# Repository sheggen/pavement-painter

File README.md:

# Raspberry Pi-controlled pavement painter

Pavement Painter is a Raspberry Pi controlled set of solenoids designed to print images to pavement using rain water. To use the Pavement Painter, you'll need to create the boards included in the Eagle files, as well as a few other controls. 

### WARNING:

Taking on this project is not for the faint at heart; there'll be lots of technical hiccups that you'll run into, and will have to solve on your own. There's hardware in addition to the software that you'll need to create, so get your soldering iron hot.  

## Requirements

- Raspberry Pi
- Python 3
- Everything included in requirements.txt and setup.sh (installable by running ```source setup.sh```)
- Physical boards (layouts included in the Pavement-painter directory)

## Installation

The code comes with a setup script. First do the apt-get installs listed at the beginning of the script. Then, running it should set up a Python Virtual Environment and pip install all the necessary components. Make sure the venv is activated before running the code, to ensure dependencies exist. To run the setup script, at the terminal enter ```source setup.sh```

## Usage

The code can most easily be ran at the terminal by running ```source run_at_boot.sh```. On the Pi, it is recommended that you do NOT run it using Thonny, as it causes a delay that will distort the print. At the terminal, we have yet to experience a delay in the printing outside of the physical limitations of the solenoids. 

## Modifying print parameters

Eventually parameters will be passed in through the above command. For now, though, I've placed all parameters at the ```__init__()``` method of the PavementPainter() class. Modify them and see what happens to your prints!

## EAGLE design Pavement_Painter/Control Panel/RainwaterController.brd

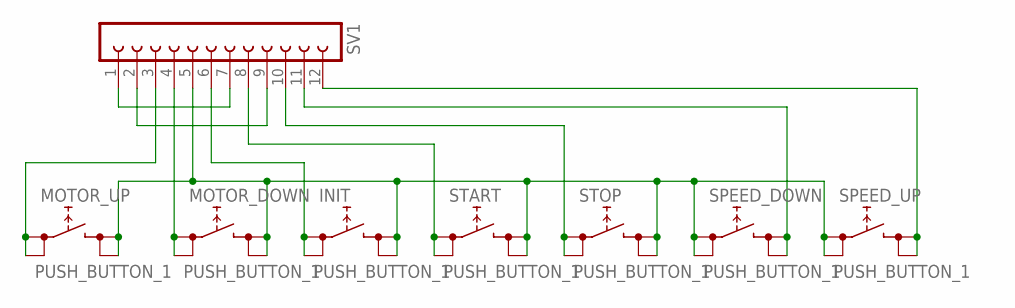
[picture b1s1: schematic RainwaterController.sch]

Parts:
INIT: PUSH_BUTTON_1; PUSHBUTTON
MOTOR_DOWN: PUSH_BUTTON_1; PUSHBUTTON
MOTOR_UP: PUSH_BUTTON_1; PUSHBUTTON
SPEED_DOWN: PUSH_BUTTON_1; PUSHBUTTON
SPEED_UP: PUSH_BUTTON_1; PUSHBUTTON
START: PUSH_BUTTON_1; PUSHBUTTON
STOP: PUSH_BUTTON_1; PUSHBUTTON
SV1: FE12-1; FE12

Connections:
unnamed: MOTOR_UP.P$1 (P1), MOTOR_UP.P$2 (P2), SV1.3
unnamed: SV1.1, SV1.7
unnamed: INIT.P$3 (P3), INIT.P$4 (P4), MOTOR_DOWN.P$3 (P3), MOTOR_DOWN.P$4 (P4), MOTOR_UP.P$3 (P3), MOTOR_UP.P$4 (P4), SPEED_DOWN.P$1 (P1), SPEED_DOWN.P$2 (P2), SPEED_UP.P$1 (P1), SPEED_UP.P$2 (P2), START.P$3 (P3), START.P$4 (P4), STOP.P$3 (P3), STOP.P$4 (P4), SV1.5
unnamed: SV1.2, SV1.9
unnamed: INIT.P$1 (P1), INIT.P$2 (P2), SV1.6
unnamed: START.P$1 (P1), START.P$2 (P2), SV1.8
unnamed: STOP.P$1 (P1), STOP.P$2 (P2), SV1.10
unnamed: MOTOR_DOWN.P$1 (P1), MOTOR_DOWN.P$2 (P2), SV1.4
unnamed: SPEED_DOWN.P$3 (P3), SPEED_DOWN.P$4 (P4), SV1.11
unnamed: SPEED_UP.P$3 (P3), SPEED_UP.P$4 (P4), SV1.12

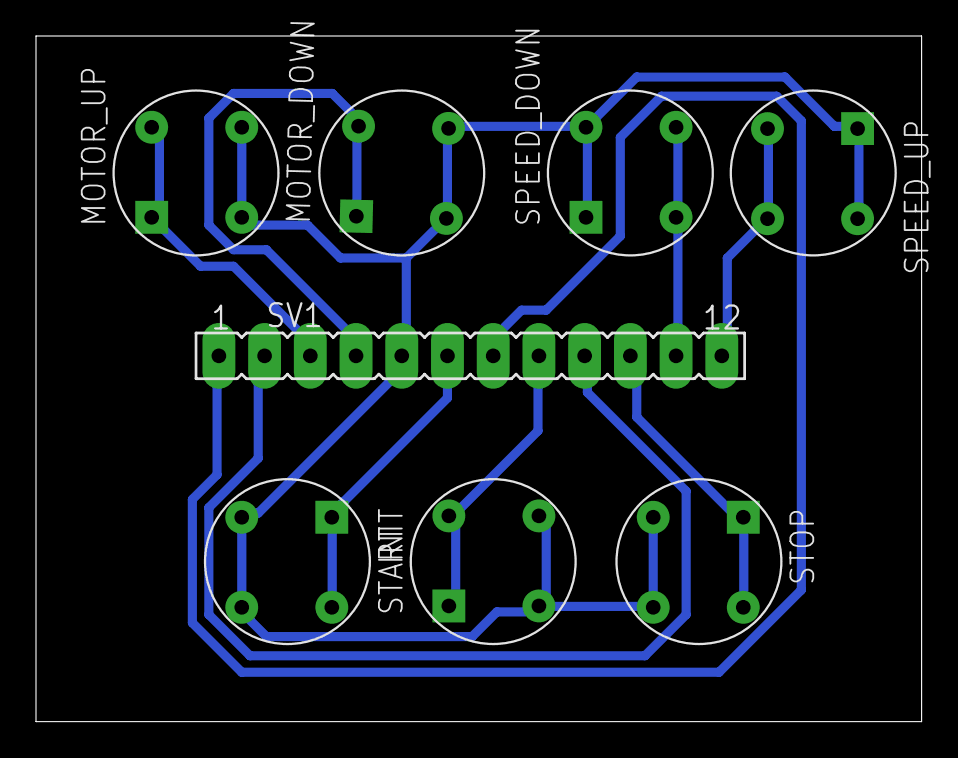
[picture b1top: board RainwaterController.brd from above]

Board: 2 copper layers, 49.2 x 38.1 mm, 8 parts (0 on the bottom side), 10 nets.

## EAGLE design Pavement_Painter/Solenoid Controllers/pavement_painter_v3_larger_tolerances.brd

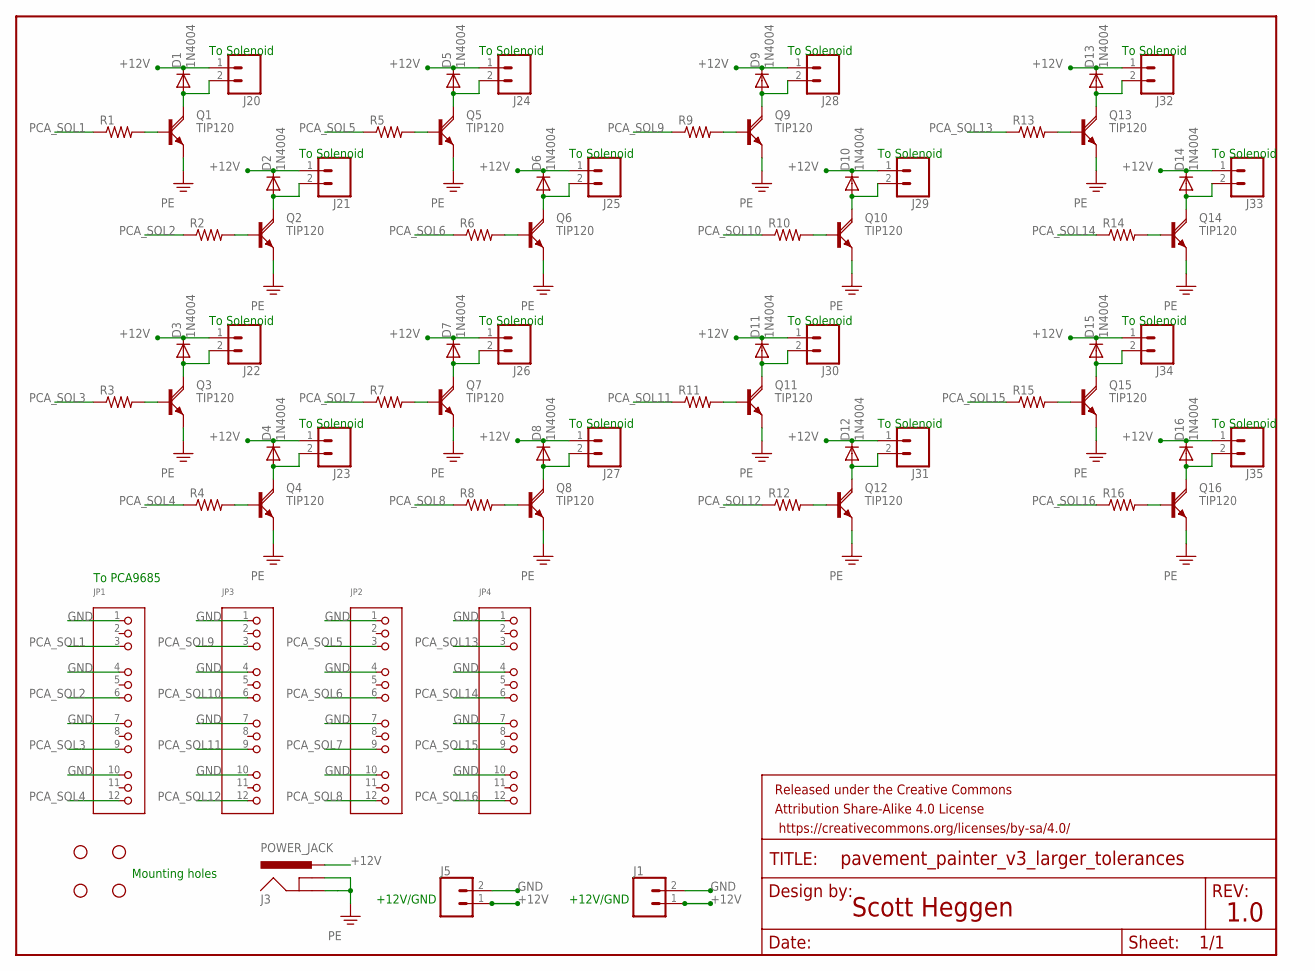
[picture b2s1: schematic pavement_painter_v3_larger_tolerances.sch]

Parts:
D1, D2, D3, D4, D5, D6, D7, D8, D9, D10, D11, D12, D13, D14, D15, D16: 1N4004; DO41-10
FRAME1: FRAME-LETTER; CREATIVE_COMMONS
H1, H2, H3, H4: STAND-OFF
J1, J5, J20, J21, J22, J23, J24, J25, J26, J27, J28, J29, J30, J31, J32, J33, J34, J35: CONN_02SCREWTERMINAL-200MIL-400MIL; SCREWTERMINAL-5MM-2-400MIL
J3: POWER_JACK; POWER_JACK_PTH
JP1, JP2, JP3, JP4: HEADER-3X04; 3X04
Q1, Q2, Q3, Q4, Q5, Q6, Q7, Q8, Q9, Q10, Q11, Q12, Q13, Q14, Q15, Q16: TIP120; BD679V
R1, R2, R3, R4, R5, R6, R7, R8, R9, R10, R11, R12, R13, R14, R15, R16: R-US_0207/10; 0207/10

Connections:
+12V: D1.C, D2.C, D3.C, D4.C, D5.C, D6.C, D7.C, D8.C, D9.C, D10.C, D11.C, D12.C, D13.C, D14.C, D15.C, D16.C, J1.1, J3.PWR, J5.1, J20.1, J21.1, J22.1, J23.1, J24.1, J25.1, J26.1, J27.1, J28.1, J29.1, J30.1, J31.1, J32.1, J33.1, J34.1, J35.1
GND: J1.2, J3.GND, J3.GNDBREAK, J5.2, JP1.1, JP1.4, JP1.7, JP1.10, JP2.1, JP2.4, JP2.7, JP2.10, JP3.1, JP3.4, JP3.7, JP3.10, JP4.1, JP4.4, JP4.7, JP4.10, Q1.E, Q2.E, Q3.E, Q4.E, Q5.E, Q6.E, Q7.E, Q8.E, Q9.E, Q10.E, Q11.E, Q12.E, Q13.E, Q14.E, Q15.E, Q16.E
unnamed: D2.A, J21.2, Q2.C
unnamed: Q2.B, R2.2
unnamed: D1.A, J20.2, Q1.C
unnamed: Q1.B, R1.2
unnamed: D3.A, J22.2, Q3.C
unnamed: Q3.B, R3.2
unnamed: D4.A, J23.2, Q4.C
unnamed: Q4.B, R4.2
unnamed: D5.A, J24.2, Q5.C
unnamed: Q5.B, R5.2
unnamed: D6.A, J25.2, Q6.C
unnamed: Q6.B, R6.2
unnamed: D7.A, J26.2, Q7.C
unnamed: Q7.B, R7.2
unnamed: D8.A, J27.2, Q8.C
unnamed: Q8.B, R8.2
unnamed: D9.A, J28.2, Q9.C
unnamed: Q9.B, R9.2
unnamed: D10.A, J29.2, Q10.C
unnamed: Q10.B, R10.2
unnamed: D11.A, J30.2, Q11.C
unnamed: Q11.B, R11.2
unnamed: D12.A, J31.2, Q12.C
unnamed: Q12.B, R12.2
unnamed: D13.A, J32.2, Q13.C
unnamed: Q13.B, R13.2
unnamed: D14.A, J33.2, Q14.C
unnamed: Q14.B, R14.2
unnamed: D15.A, J34.2, Q15.C
unnamed: Q15.B, R15.2
unnamed: D16.A, J35.2, Q16.C
unnamed: Q16.B, R16.2
PCA_SOL1: JP1.3, R1.1
PCA_SOL2: JP1.6, R2.1
PCA_SOL3: JP1.9, R3.1
PCA_SOL4: JP1.12, R4.1
PCA_SOL5: JP2.3, R5.1
PCA_SOL6: JP2.6, R6.1
PCA_SOL7: JP2.9, R7.1
PCA_SOL8: JP2.12, R8.1
PCA_SOL9: JP3.3, R9.1
PCA_SOL10: JP3.6, R10.1
PCA_SOL11: JP3.9, R11.1
PCA_SOL12: JP3.12, R12.1
PCA_SOL13: JP4.3, R13.1
PCA_SOL14: JP4.6, R14.1
PCA_SOL15: JP4.9, R15.1
PCA_SOL16: JP4.12, R16.1

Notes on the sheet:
To Solenoid
To PCA9685
+12V/GND
Scott Heggen
1.0
Mounting holes

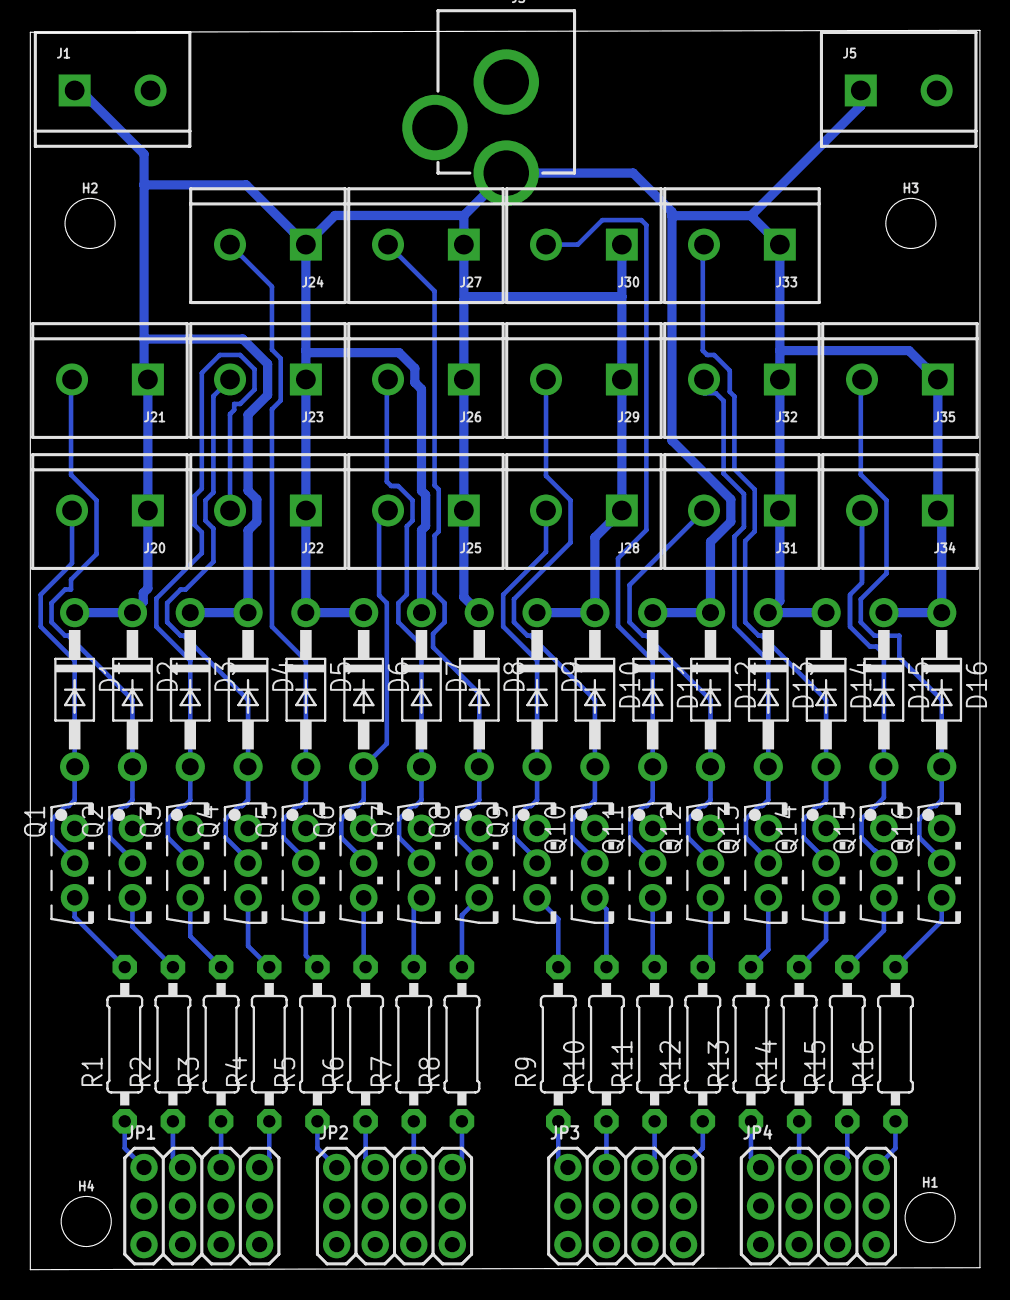
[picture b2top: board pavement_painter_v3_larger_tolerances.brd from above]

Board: 2 copper layers, 62.6 x 81.7 mm, 76 parts (0 on the bottom side), 50 nets.

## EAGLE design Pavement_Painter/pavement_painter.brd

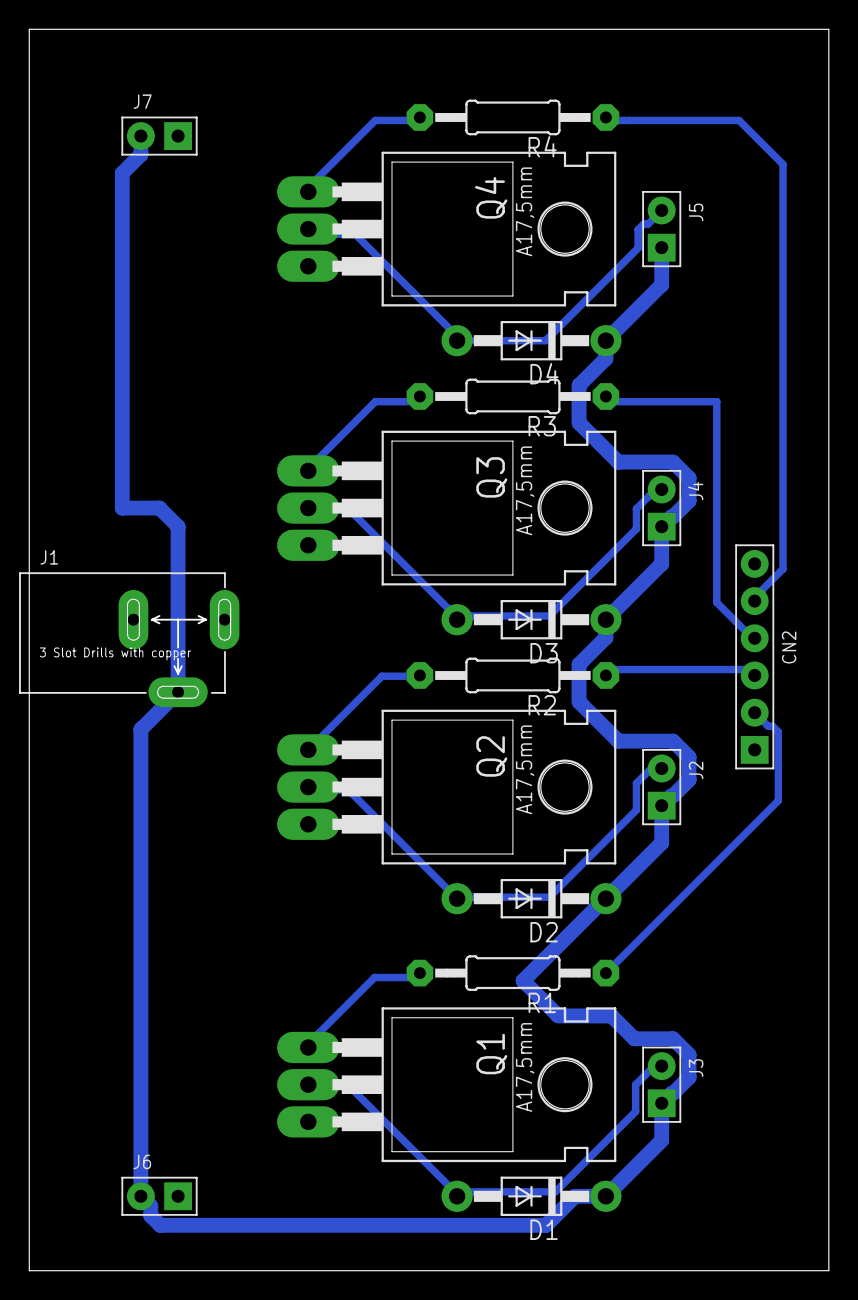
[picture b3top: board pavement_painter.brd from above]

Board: 2 copper layers, 54.5 x 84.6 mm, 21 parts (0 on the bottom side), 14 nets.

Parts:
CN2: 6p-2.54; H6-2.54
D1, D2, D3, D4: 1N4004; DO41-10
FRAME1: FRAME-LETTER; CREATIVE_COMMONS
J1: DC-005; DCJ3P-14.2X11.0X9.0MM
J2, J3, J4, J5: H2-2.54
J6, J7: 2p-2.54; H2-2.54
Q1, Q2, Q3, Q4: TIP120; TO220AH
R1, R2, R3, R4: 0207/12

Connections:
+12V: D1.C, D2.C, D3.C, D4.C, J1.-2, J2.1, J3.1, J4.1, J5.1, J6.2, J7.2
GND: CN2.1, J1.+, J1.-1, J6.1, J7.1, Q1.E, Q2.E, Q3.E, Q4.E
unnamed: D2.A, J2.2, Q2.C
unnamed: Q2.B, R2.2
unnamed: D1.A, J3.2, Q1.C
unnamed: Q1.B, R1.2
unnamed: D3.A, J4.2, Q3.C
unnamed: Q3.B, R3.2
unnamed: D4.A, J5.2, Q4.C
unnamed: Q4.B, R4.2
PCA_PIN1: CN2.2, R1.1
PCA_PIN2: CN2.3, R2.1
PCA_PIN3: CN2.4, R3.1
PCA_PIN4: CN2.5, R4.1

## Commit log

2019-03-16 Base code started; parses any image, converts to binary image, resizes to right number of solenoids, and fires them sequentially.
2019-03-16 Updating code with documentation, and notes about what to do next.
2019-03-16 Reversed order of image processing to make it miniscually faster.
2019-03-16 Minor cleanup of language
2019-03-20 Adding starter code for PCA integration
2019-03-20 working on getting PCA working
2019-03-21 Code appears to work; scales to any number of nozzles
2019-03-21 Adding documentation
2019-03-21 Bug fixes with image height and PCA needs a frequency to run LEDs at!
2019-03-21 tested with up to 3 PCAs!
2019-03-22 Working on speeding up solenoid firing rata
2019-03-23 Added Eagle files
2019-03-23 Removing temp files
2019-03-30 Updated to handle 16 solenoids on a single board, plus fixed issues with first version
2019-04-02 Newest version with fixes from v3
2019-04-02 Minor layout updates
2019-04-02 Layout with tighter dimension
2019-04-02 Adding code to work with ODB sensor
2019-04-02 Attempting to modify fire/stop fire behavior to only stop if color changes
2019-04-04 Diodes removed, relayed out
2019-04-04 Very minor adjustments made to layout
2019-04-06 Updating jumper numbers, slight changes to layout
2019-04-06 Got OBD2 working; updated main with OBD2 calls. Needs testing
2019-04-06 Updated OBD2 class to handle shots per second.
2019-04-08 Debugging firing + speed control
2019-04-09 Working on getting firing to work right.
2019-04-10 Test code for OBD added; debugged firing of 45 solenoids
2019-04-13 Behind a few commits; this one worked after first road test; OBD has issues though
2019-04-13 Adding new files which are important, such as sample images and run_at_boot.sh
2019-04-16 incremental progress on improving printing
2019-04-22 Creating setup.sh because it got deleted somehow
2019-04-22 Getting README started
2019-04-27 committing recent changes; mostly file upload differences
2019-05-08 Updating OBD2 and main to work with cars
2019-05-09 Adding LiveCamera.py
2019-05-09 Copying over LiveCamera.py again
2019-05-12 Camera server now integrated with main code
2019-05-13 Fixed live camera to show speed
2019-05-14 Adding time measurements
2019-05-14 getting sparse image to work
2019-05-14 Updating code with sparse matrix plus fixing speed problems
2019-05-14 Got printer running about 2.5x faster than best print, but not tested!
2019-05-15 Changing sparse image to dictionary
2019-05-15 Updating sparse image code to work
2019-05-15 Now fires from dictionary as well as list (commented out)
2019-05-15 Minor code cleanup whilest I think.
2019-05-15 Last push before editing on Pi instead of Mac
2019-05-21 Moving files
2019-05-21 IS this how you delete?
2019-05-21 Dir needs a file
2019-05-21 Removing old files
2019-05-22 Committing Jed's files for the control panel
2019-07-22 Building foundation for the web server
2019-07-23 Adding webserver with livefeed
2019-07-25 setting up web server
2019-07-25 Reverting out bad imports
2019-07-25 missed one
2019-07-26 Web server testing
2019-07-26 Webserver is working with live feed!
2019-07-30 modifying button layout
2019-07-30 adding glyphicons to buttons
2019-07-30 Webserver interactions with pavementprinter object added...
2019-07-30 Webserver talking to pavement printer code now
2019-07-31 Handling button holds
2019-07-31 Adding event listeners to buttons
2019-07-31 Button listeners work with holding down
2019-07-31 Button coloring and interaction with controller working
2019-07-31 Should now parse an image when selected in UI
2019-07-31 Webserver buttons work as expected now
2019-07-31 Painting is working!
2019-07-31 Start/stop and flushing can now be turned off and on
2019-09-11 streamlining requirements.txt to remove unnecessary duplicates
2019-11-02 Bump pillow from 6.1.0 to 6.2.0 in /webServer
    Bumps [pillow](https://github.com/python-pillow/Pillow) from 6.1.0 to 6.2.0.
    - [Release notes](https://github.com/python-pillow/Pillow/releases)
    - [Changelog](https://github.com/python-pillow/Pillow/blob/master/CHANGES.rst)
    - [Commits](https://github.com/python-pillow/Pillow/compare/6.1.0...6.2.0)
2021-03-19 Bump pillow from 6.1.0 to 8.1.1 in /webServer
    Bumps [pillow](https://github.com/python-pillow/Pillow) from 6.1.0 to 8.1.1.
    - [Release notes](https://github.com/python-pillow/Pillow/releases)
    - [Changelog](https://github.com/python-pillow/Pillow/blob/master/CHANGES.rst)
    - [Commits](https://github.com/python-pillow/Pillow/compare/6.1.0...8.1.1)
2021-03-20 Bump jinja2 from 2.10.1 to 2.11.3 in /webServer
    Bumps [jinja2](https://github.com/pallets/jinja) from 2.10.1 to 2.11.3.
    - [Release notes](https://github.com/pallets/jinja/releases)
    - [Changelog](https://github.com/pallets/jinja/blob/master/CHANGES.rst)
    - [Commits](https://github.com/pallets/jinja/compare/2.10.1...2.11.3)
2021-03-25 Bump pyyaml from 5.1.1 to 5.4 in /webServer
    Bumps [pyyaml](https://github.com/yaml/pyyaml) from 5.1.1 to 5.4.
    - [Release notes](https://github.com/yaml/pyyaml/releases)
    - [Changelog](https://github.com/yaml/pyyaml/blob/master/CHANGES)
    - [Commits](https://github.com/yaml/pyyaml/compare/5.1.1...5.4)
2021-06-08 Bump pillow from 6.1.0 to 8.2.0 in /webServer
    Bumps [pillow](https://github.com/python-pillow/Pillow) from 6.1.0 to 8.2.0.
    - [Release notes](https://github.com/python-pillow/Pillow/releases)
    - [Changelog](https://github.com/python-pillow/Pillow/blob/master/CHANGES.rst)
    - [Commits](https://github.com/python-pillow/Pillow/compare/6.1.0...8.2.0)
    ---
    updated-dependencies:
2021-09-08 Bump pillow from 6.1.0 to 8.3.2 in /webServer
    Bumps [pillow](https://github.com/python-pillow/Pillow) from 6.1.0 to 8.3.2.
    - [Release notes](https://github.com/python-pillow/Pillow/releases)
    - [Changelog](https://github.com/python-pillow/Pillow/blob/master/CHANGES.rst)
    - [Commits](https://github.com/python-pillow/Pillow/compare/6.1.0...8.3.2)
    ---
    updated-dependencies:
2022-01-13 Bump pillow from 6.1.0 to 9.0.0 in /webServer
    Bumps [pillow](https://github.com/python-pillow/Pillow) from 6.1.0 to 9.0.0.
    - [Release notes](https://github.com/python-pillow/Pillow/releases)
    - [Changelog](https://github.com/python-pillow/Pillow/blob/main/CHANGES.rst)
    - [Commits](https://github.com/python-pillow/Pillow/compare/6.1.0...9.0.0)
    ---
    updated-dependencies:
2022-03-11 Bump pillow from 6.1.0 to 9.0.1 in /webServer
    Bumps [pillow](https://github.com/python-pillow/Pillow) from 6.1.0 to 9.0.1.
    - [Release notes](https://github.com/python-pillow/Pillow/releases)
    - [Changelog](https://github.com/python-pillow/Pillow/blob/main/CHANGES.rst)
    - [Commits](https://github.com/python-pillow/Pillow/compare/6.1.0...9.0.1)
    ---
    updated-dependencies:
2022-06-21 Bump numpy from 1.16.4 to 1.22.0 in /webServer
    Bumps [numpy](https://github.com/numpy/numpy) from 1.16.4 to 1.22.0.
    - [Release notes](https://github.com/numpy/numpy/releases)
    - [Changelog](https://github.com/numpy/numpy/blob/main/doc/HOWTO_RELEASE.rst)
    - [Commits](https://github.com/numpy/numpy/compare/v1.16.4...v1.22.0)
    ---
    updated-dependencies:
2022-11-22 Bump pillow from 6.1.0 to 9.3.0 in /webServer
    Bumps [pillow](https://github.com/python-pillow/Pillow) from 6.1.0 to 9.3.0.
    - [Release notes](https://github.com/python-pillow/Pillow/releases)
    - [Changelog](https://github.com/python-pillow/Pillow/blob/main/CHANGES.rst)
    - [Commits](https://github.com/python-pillow/Pillow/compare/6.1.0...9.3.0)
    ---
    updated-dependencies:

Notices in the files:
parts and their libraries:
SparkFun-Aesthetics: Licensing: Creative Commons ShareAlike 4.0 International - https://creativecommons.org/licenses/by-sa/4.0
SparkFun-Aesthetics: Released under the Creative Commons Attribution Share-Alike 4.0 License
SparkFun-Aesthetics: https://creativecommons.org/licenses/by-sa/4.0
